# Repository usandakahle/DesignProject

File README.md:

# Micromouse Power Module System

This project is the power module circuit for the EEE3088F design project that provides power to the micromouse system

## Features

-  Boost Converter (3.7V → 5V @ 1.5A)
-  LDO Regulator (5V → 3.3V @ 300mA)
-  Dual H-Bridge Motor Driver (DRV8833 for 4x brushed DC motors)
-  High-Side Load Switches (TPS2HB50-Q1, 2 channels @ 1A each)
-  Physical ON/OFF switch with <30µA shutdown current
-  USB-C Female Connector
-  CH224K PD Negotiation (9V)
-  Linear Voltage Regulator, LM7805 (5V)
-  LiPo Battery Charging IC, TC4056A
-  Small PCB footprint, JLCPCB-ready
-  -All features and components are sourced from JLCPCB (https://jlcpcb.com/parts/all-electronic-components) 
  
---

##  Design Overview

- Input: 3.7V Li-ion (1S1P)
- USB-C Input: 9V
- Voltage Regulation:
  - Boost: MT3608
  - 3.3V Regulator: AMS1117-3.3 or TLV75533P
  - 5V Regulator: LM7805
- Motor Driver: DRV8833, controls 4 DC motors bidirectionally
- Load Switches:TPS2HB50-Q1 with configurable ILIM resistors
- ON/OFF Circuit: Slide switch + pMOS + NPN low-quiescent design

---

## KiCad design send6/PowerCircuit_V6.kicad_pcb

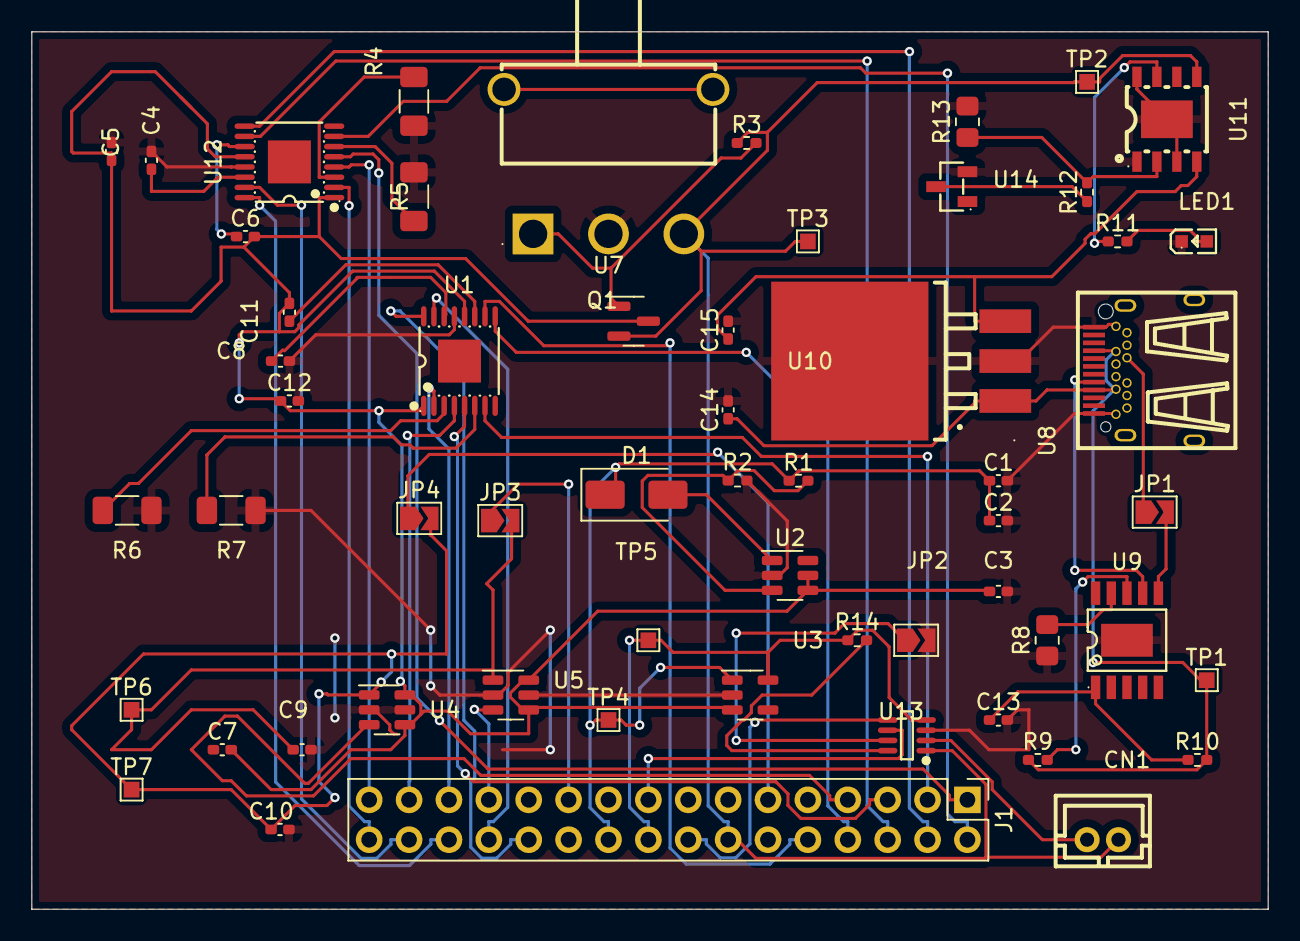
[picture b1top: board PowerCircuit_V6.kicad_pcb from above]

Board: 2 copper layers, 78.7 x 55.9 mm, 58 parts (0 on the bottom side), 55 nets.

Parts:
C1, C2, C3, C7, C9, C10, C13: 1uF; C_0402_1005Metric_Pad0.74x0.62mm_HandSolder
C4, C8: 2.2 uF; C_0402_1005Metric_Pad0.74x0.62mm_HandSolder
C5, C12: 10 uF; C_0402_1005Metric_Pad0.74x0.62mm_HandSolder
C6, C11: 10nF; C_0402_1005Metric_Pad0.74x0.62mm_HandSolder
C14, C15: 10uF; C_0402_1005Metric_Pad0.74x0.62mm_HandSolder
CN1: B2B-PH-K-S(LF)(SN); CONN-TH_B2B-PH-K-S
D1: D_Schottky; D_SMA
J1: Conn_02x16_Odd_Even; PinHeader_2x16_P2.54mm_Vertical
JP1, JP2, JP3, JP4: Jumper_2_Open; SolderJumper-2_P1.3mm_Open_TrianglePad1.0x1.5mm
LED1: KT-0603R; LED0603-RD
Q1: AO3401A; SOT-23
R1: 75k; R_0402_1005Metric_Pad0.72x0.64mm_HandSolder
R2, R9: 10k; R_0402_1005Metric_Pad0.72x0.64mm_HandSolder
R3: 47k; R_0402_1005Metric_Pad0.72x0.64mm_HandSolder
R4, R5, R6, R7: 1; R_1206_3216Metric_Pad1.30x1.75mm_HandSolder
R8: 6.8k; R_0805_2012Metric_Pad1.20x1.40mm_HandSolder
R10, R11, R14: 1k; R_0402_1005Metric_Pad0.72x0.64mm_HandSolder
R12: 2k; R_0402_1005Metric_Pad0.72x0.64mm_HandSolder
R13: 5.6k; R_0805_2012Metric_Pad1.20x1.40mm_HandSolder
TP1, TP2, TP3: TestPoint; TestPoint_Pad_1.0x1.0mm
TP4: 5V out; TestPoint_Pad_1.0x1.0mm
TP5: 3.3V out; TestPoint_Pad_1.0x1.0mm
TP6: External Load out; TestPoint_Pad_1.0x1.0mm
TP7: Ext load out; TestPoint_Pad_1.0x1.0mm
U1, U12: DRV8833PWP; TSSOP-16_L5.0-W4.4-P0.65-LS6.4-BL-EP
U2: MT3608; SOT-23-6
U3: AP2112K-3.3; SOT-23-5
U4, U5: TPS22929D; SOT-23-6
U7: K3-1391B-51; SW-TH_K3-1391B-51
U8: FUC-24F11-SNLB1; USB-C-SMD_C67380
U9: CH224K; ESSOP-10_L4.9-W3.9-P1.0-LS6.0-TL-EP
U10: LM7805S/TR; TO-263-3_L8.6-W10.2-P2.54-LS14.4-BR
U11: TC4056A; ESOP-8_L4.9-W3.9-P1.27-LS6.0-BR-EP3.3
U13: INA219AIDCNR; SOT-23-8_L3.0-W1.7-P0.65-LS2.8-BR
U14: MMBT2222A_C8512; SOT-23-3_L2.9-W1.3-P1.90-LS2.4-BR

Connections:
/3V3: J1.18, R14.1, TP5.1, U3.5 (VOUT), U13.4 (VS)
/5V: C1.1, C2.1, D1.1 (K), J1.20, R1.1, TP4.1, U3.1 (VIN)
/BATTERY: CN1.1, J1.14, Q1.2 (S), R3.1, TP2.1, TP3.1, U7.3, U11.5 (BAT), U13.1 (IN+)
/BATT_OUT: CN1.2, U13.2 (IN-)
/CC1: U8.A5 (CC1), U9.7 (CC1)
/CC2: JP1.2 (B), U9.6 (CC2)
/CTRL_EXT_LOAD1: J1.25, U5.3 (ON)
/CTRL_EXT_LOAD2: J1.7, U4.3 (ON)
/EXT_LOAD1_OUT: J1.21, JP3.1 (A)
/EXT_LOAD2_OUT: J1.11, JP4.1 (A)
/I2C1_SCL: J1.16, U13.5 (SCL)
/I2C1_SDA: J1.17, U13.6 (SDA)
/MOTOR1_A_OUT: J1.32, U12.2 (AOUT1)
/MOTOR1_B_OUT: J1.31, U12.4 (AOUT2)
/MOTOR1_CTRL1: J1.28, U12.16 (AIN1)
/MOTOR1_CTRL2: J1.30, U12.15 (AIN2)
/MOTOR2_A_OUT: J1.2, U12.7 (BOUT1)
/MOTOR2_B_OUT: J1.1, U12.5 (BOUT2)
/MOTOR2_CTRL1: J1.4, U12.9 (BIN1)
/MOTOR2_CTRL2: J1.6, U12.10 (BIN2)
/MOTOR3_A_OUT: J1.27, U1.2 (AOUT1)
/MOTOR3_B_OUT: J1.29, U1.4 (AOUT2)
/MOTOR3_CTRL1: J1.24, U1.16 (AIN1)
/MOTOR3_CTRL2: J1.26, U1.15 (AIN2)
/MOTOR4_A_OUT: J1.3, U1.7 (BOUT1)
/MOTOR4_B_OUT: J1.5, U1.5 (BOUT2)
/MOTOR4_CTRL1: J1.8, U1.9 (BIN1)
/MOTOR4_CTRL2: J1.10, U1.10 (BIN2)
/PROG: R12.2, R13.1, U11.2 (PROG)
/PWR_OUT: C3.1, C5.1, C6.2, C7.2, C11.2, C12.1, Q1.3 (D), U1.1 (nSleep), U1.12 (VM), U2.4 (EN), U2.5 (IN), U3.3 (EN), U4.4 (VIN), U4.6 (VIN), U5.4 (VIN), U5.6 (VIN), U12.1 (nSleep), U12.12 (VM)
/Step_5V: C15.1, U10.3 (OUT), U11.4 (VCC)
/VBUS: C14.1, R9.1, R10.2, TP1.1, U8.A4 (VBUS), U8.A9 (VBUS), U8.B4 (VBUS), U8.B9 (VBUS), U10.1 (VCC)
GND: C1.2, C2.2, C3.2, C4.2, C5.2, C7.1, C8.2, C9.2, C10.2, C12.2, C13.2, C14.2, C15.2, J1.19, J1.23, JP2.2 (B), LED1.1 (K), R2.2, R4.1, R5.2, R6.1, R7.2, R8.1, R13.2, U1.13 (GND), U2.2 (GND), U3.2 (GND), U4.2 (GND), U4.5 (GND), U5.2 (GND), U5.5 (GND), U7.2, U8.A1 (GND), U8.A12 (GND), U8.B1 (GND), U8.B12 (GND), U9.11 (GND), U10.2 (GND), U10.4 (GND), U11.1 (TEMP), U11.3 (GND), U11.8 (CE), U11.9 (EP), U12.13 (GND), U13.3 (GND), U14.2 (E)
unnamed: D1.2 (A), U2.1 (SW)
unnamed: JP1.1 (A), U8.B5 (CC2)
unnamed: JP2.1 (A), U13.7 (A0)
unnamed: C9.1, JP3.2 (B), TP6.1, U5.1 (VOUT)
unnamed: C10.1, JP4.2 (B), TP7.1, U4.1 (VOUT)
unnamed: LED1.2 (A), R11.2
unnamed: Q1.1 (G), R3.2, U7.1
unnamed: R6.2, U1.3 (AISEN)
unnamed: R7.1, U1.6 (BISEN)
unnamed: C11.1, U1.11 (VCP)
unnamed: C8.1, U1.14 (VINT)
unnamed: R1.2, R2.1, U2.3 (FB)
unnamed: R8.2, U9.9 (CFG1)
unnamed: R9.2, U9.8 (VBUS)
unnamed: C13.1, R10.1, U9.1 (VDD)
unnamed: R11.1, U11.7 (CHRG)
unnamed: R4.2, U12.3 (AISEN)
unnamed: R5.1, U12.6 (BISEN)
unnamed: C6.1, U12.11 (VCP)
unnamed: C4.1, U12.14 (VINT)
unnamed: R14.2, U13.8 (A1)
unnamed: R12.1, U14.3 (C)

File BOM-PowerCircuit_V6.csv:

Comment,Designator,Footprint,LCSC,Quantity
1k,"R10,R11,R14",R_0402_1005Metric_Pad0.72x0.64mm_HandSolder,C11702,3
2.2 uF,"C4,C8",C_0402_1005Metric_Pad0.74x0.62mm_HandSolder,C12530,2
AO3401A,Q1,SOT-23,C15127,1
10nF,C6,C_0402_1005Metric_Pad0.74x0.62mm_HandSolder,C15195,1
10nF,"C11,C12,C14,C15,C5",C_0402_1005Metric_Pad0.74x0.62mm_HandSolder,C15525,5
6.8k,R8,R_0805_2012Metric_Pad1.20x1.40mm_HandSolder,C17772,1
1,"R4,R5,R6,R7",R_1206_3216Metric_Pad1.30x1.75mm_HandSolder,C17928,4
KT-0603R,LED1,LED0603-RD,C2286,1
75k,R1,R_0603_1608Metric_Pad0.98x0.95mm_HandSolder,C23242,1
D_Schottky,D1,D_SMA,C2480,1
10k,"R2,R9",R_0402_1005Metric_Pad0.72x0.64mm_HandSolder,C25744,2
47k,R3,R_0402_1005Metric_Pad0.72x0.64mm_HandSolder,C25792,1
2k,R12,R_0402_1005Metric_Pad0.72x0.64mm_HandSolder,C4109,1
TPS22929D,"U4,U5",SOT-23-6,C415177,2
5.6k,R13,R_0805_2012Metric_Pad1.20x1.40mm_HandSolder,C4382,1
DRV8833PWP,"U1,U12",TSSOP-16_L5.0-W4.4-P0.65-LS6.4-BL-EP,C50506,2
LM7805S/TR,U10,TO-263-3_L8.6-W10.2-P2.54-LS14.4-BR,C507146,1
AP2112K-3.3,U3,SOT-23-5,C51118,1
1uF,"C1,C10,C13,C2,C3,C7,C9",C_0402_1005Metric_Pad0.74x0.62mm_HandSolder,C52923,7
FUC-24F11-SNLB1,U8,USB-C-SMD_C67380,C67380,1
TC4056A,U11,ESOP-8_L4.9-W3.9-P1.27-LS6.0-BR-EP3.3,C84051,1
MT3608,U2,SOT-23-6,C84817,1
MMBT2222A_C8512,U14,SOT-23-3_L2.9-W1.3-P1.90-LS2.4-BR,C8512,1
INA219AIDCNR,U13,SOT-23-8_L3.0-W1.7-P0.65-LS2.8-BR,C87469,1
K3-1391B-51,U7,SW-TH_K3-1391B-51,C92656,1
CH224K,U9,ESSOP-10_L4.9-W3.9-P1.0-LS6.0-TL-EP,C970725,1
External Load out,TP6,TestPoint_Pad_1.0x1.0mm,,1
TestPoint,TP3,TestPoint_Pad_1.0x1.0mm,,1
Jumper_2_Open,JP3,SolderJumper-2_P1.3mm_Open_TrianglePad1.0x1.5mm,,1
TestPoint,TP2,TestPoint_Pad_1.0x1.0mm,,1
3.3V out,TP5,TestPoint_Pad_1.0x1.0mm,,1
Jumper_2_Open,JP1,SolderJumper-2_P1.3mm_Open_TrianglePad1.0x1.5mm,,1
5V out,TP4,TestPoint_Pad_1.0x1.0mm,,1
Jumper_2_Open,JP4,SolderJumper-2_P1.3mm_Open_TrianglePad1.0x1.5mm,,1
Jumper_2_Open,JP2,SolderJumper-2_P1.3mm_Open_TrianglePad1.0x1.5mm,,1
Ext load out,TP7,TestPoint_Pad_1.0x1.0mm,,1
TestPoint,TP1,TestPoint_Pad_1.0x1.0mm,,1

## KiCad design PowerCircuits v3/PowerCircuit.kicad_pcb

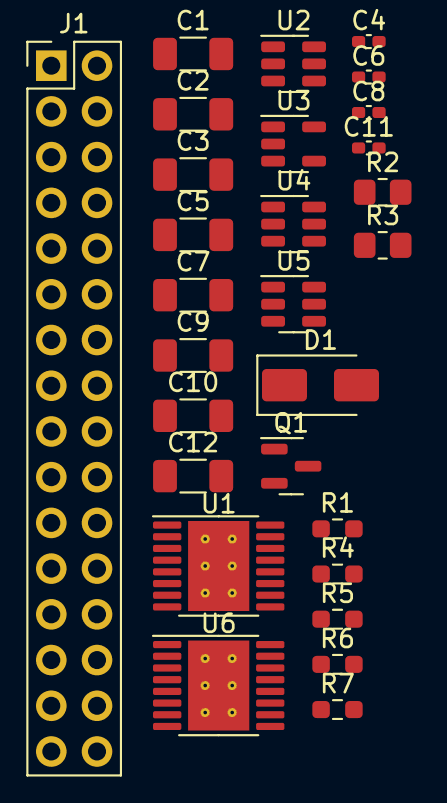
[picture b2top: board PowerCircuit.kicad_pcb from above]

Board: 2 copper layers, 28 parts (0 on the bottom side), 36 nets, no tracks yet.

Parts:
C1, C3, C7, C9, C10: 1uF; C_1206_3216Metric_Pad1.33x1.80mm_HandSolder
C2: 1 uF; C_1206_3216Metric_Pad1.33x1.80mm_HandSolder
C4, C11: 2.2 uF; C_0402_1005Metric_Pad0.74x0.62mm_HandSolder
C5, C12: 10 uF; C_1206_3216Metric_Pad1.33x1.80mm_HandSolder
C6, C8: 0.01uF; C_0402_1005Metric_Pad0.74x0.62mm_HandSolder
D1: D_Schottky; D_SMA
J1: Conn_02x16_Odd_Even; PinHeader_2x16_P2.54mm_Vertical
Q1: AO3401A; SOT-23
R1: 75k; R_0603_1608Metric_Pad0.98x0.95mm_HandSolder
R2: 10k; R_0805_2012Metric_Pad1.20x1.40mm_HandSolder
R3: 47k; R_0805_2012Metric_Pad1.20x1.40mm_HandSolder
R4, R5: 1; R_0603_1608Metric_Pad0.98x0.95mm_HandSolder
R6, R7: 0.4; R_0603_1608Metric_Pad0.98x0.95mm_HandSolder
U1, U6: DRV8833PWP; HTSSOP-16-1EP_4.4x5mm_P0.65mm_EP3.4x5mm_Mask2.46x2.31mm_The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
U2: MT3608; SOT-23-6
U3: AP2112K-3.3; SOT-23-5
U4, U5: TPS22929D; SOT-23-6

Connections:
/3V3: J1.18, U3.5 (VOUT)
/5V: C1.1, C2.1, D1.1 (K), J1.20, R1.1, U3.1 (VIN)
/BATTERY: J1.14, Q1.2 (S), R3.1
/CTRL_EXT_LOAD1: J1.25, U5.3 (ON)
/CTRL_EXT_LOAD2: J1.7, U4.3 (ON)
/EXT_LOAD1_OUT: C9.1, J1.21, U5.1 (VOUT)
/EXT_LOAD2_OUT: C10.1, J1.11, U4.1 (VOUT)
/MOTOR1_A_OUT: J1.32, U1.2 (AOUT1)
/MOTOR1_B_OUT: J1.31, U1.4 (AOUT2)
/MOTOR1_CTRL1: J1.28, U1.16 (AIN1)
/MOTOR1_CTRL2: J1.30, U1.15 (AIN2)
/MOTOR2_A_OUT: J1.2, U1.7 (BOUT1)
/MOTOR2_B_OUT: J1.1, U1.5 (BOUT2)
/MOTOR2_CTRL1: J1.4, U1.9 (BIN1)
/MOTOR2_CTRL2: J1.6, U1.10 (BIN2)
/MOTOR3_A_OUT: J1.27, U6.2 (AOUT1)
/MOTOR3_B_OUT: J1.29, U6.4 (AOUT2)
/MOTOR3_CTRL1: J1.24, U6.16 (AIN1)
/MOTOR3_CTRL2: J1.26, U6.15 (AIN2)
/MOTOR4_A_OUT: J1.3, U6.7 (BOUT1)
/MOTOR4_B_OUT: J1.5, U6.5 (BOUT2)
/MOTOR4_CTRL1: J1.8, U6.9 (BIN1)
/MOTOR4_CTRL2: J1.10, U6.10 (BIN2)
/PWR_OUT: C3.1, C5.1, C6.2, C7.2, C8.2, C12.1, Q1.3 (D), U1.1 (nSLEEP), U1.12 (VM), U2.4 (EN), U2.5 (IN), U3.3 (EN), U4.4 (VIN), U4.6 (VIN), U5.4 (VIN), U5.6 (VIN), U6.1 (nSLEEP), U6.12 (VM)
GND: C1.2, C2.2, C3.2, C4.2, C5.2, C7.1, C9.2, C10.2, C11.2, C12.2, J1.19, J1.23, R2.2, R4.1, R5.2, R6.2, R7.1, U1.13 (GND), U1.17 (GND(PPAD)), U2.2 (GND), U3.2 (GND), U4.2 (GND), U4.5 (GND), U5.2 (GND), U5.5 (GND), U6.13 (GND), U6.17 (GND(PPAD))
unnamed: D1.2 (A), U2.1 (SW)
unnamed: Q1.1 (G), R3.2
unnamed: R4.2, U1.3 (AISEN)
unnamed: R5.1, U1.6 (BISEN)
unnamed: C6.1, U1.11 (VCP)
unnamed: C4.1, U1.14 (VINT)
unnamed: R1.2, R2.1, U2.3 (FB)
unnamed: R6.1, U6.3 (AISEN)
unnamed: R7.2, U6.6 (BISEN)
unnamed: C8.1, U6.11 (VCP)
unnamed: C11.1, U6.14 (VINT)

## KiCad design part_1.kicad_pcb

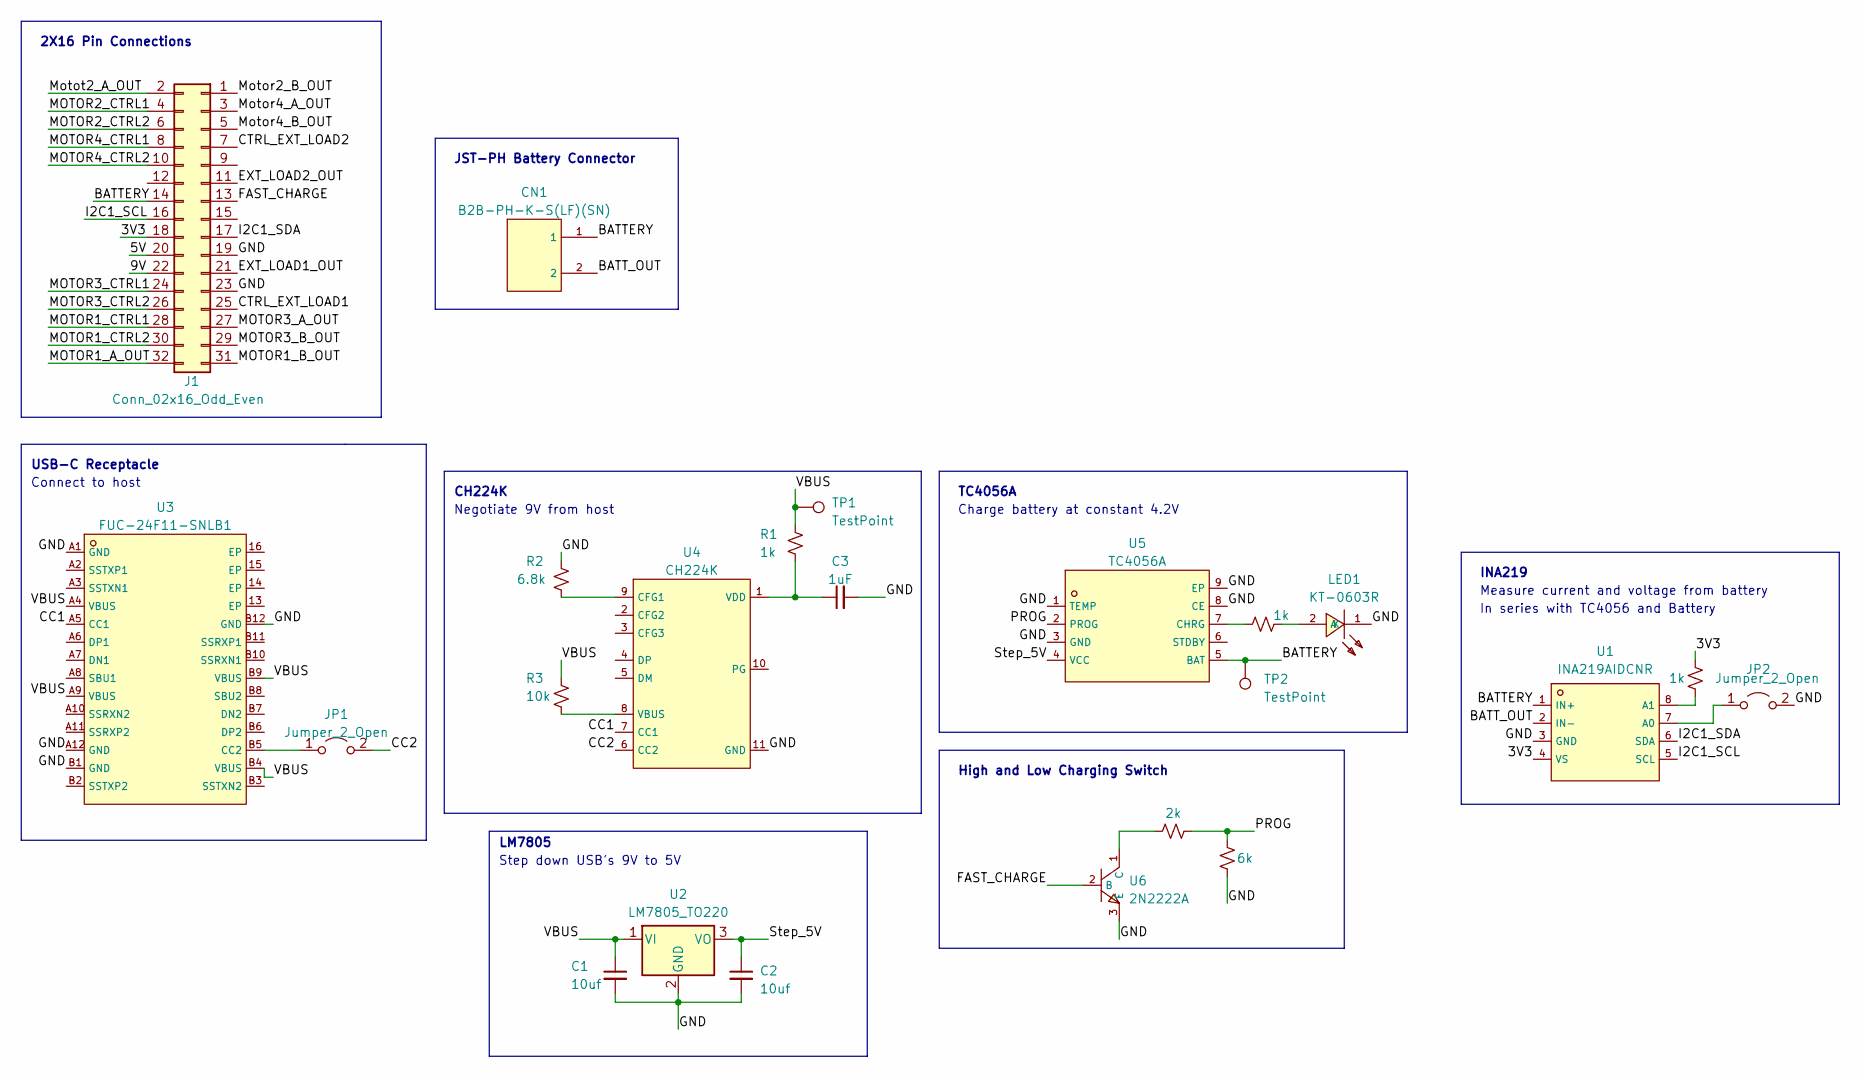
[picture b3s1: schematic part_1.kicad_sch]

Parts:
C1, C2: 10uf; C_0402_1005Metric_Pad0.74x0.62mm_HandSolder
C3: 1uF; C_0402_1005Metric_Pad0.74x0.62mm_HandSolder
CN1: B2B-PH-K-S(LF)(SN); CONN-TH_B2B-PH-K-S; LCSC C131337
J1: Conn_02x16_Odd_Even; PinHeader_2x16_P2.54mm_Vertical
JP1, JP2: Jumper_2_Open; SolderJumper-2_P1.3mm_Open_TrianglePad1.0x1.5mm
LED1: KT-0603R; LED0603-RD; LCSC C2286
R1, R4, R5: 1k; R_0402_1005Metric_Pad0.72x0.64mm_HandSolder
R2: 6.8k; R_0402_1005Metric_Pad0.72x0.64mm_HandSolder
R3: 10k; R_0402_1005Metric_Pad0.72x0.64mm_HandSolder
R6: 2k; R_0402_1005Metric_Pad0.72x0.64mm_HandSolder
R10: 6k; R_0402_1005Metric_Pad0.72x0.64mm_HandSolder
TP1, TP2: TestPoint; TestPoint_Pad_1.0x1.0mm
U1: INA219AIDCNR; SOT-23-8_L3.0-W1.7-P0.65-LS2.8-BR; LCSC C87469
U2: LM7805_TO220; TO-220-3_Vertical
U3: FUC-24F11-SNLB1; USB-C-SMD_C67380; Part # C67380
U4: CH224K; ESSOP-10_L4.9-W3.9-P1.0-LS6.0-TL-EP; Part # C970725
U5: TC4056A; ESSOP-10_L4.9-W3.9-P1.0-LS6.0-TL-EP; LCSC C84051
U6: 2N2222A; TO-92-3_L4.8-W3.7-P2.54-R; LCSC C358533

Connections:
/3V3: J1.18, R5.1, U1.4 (VS)
/5V: J1.20
/9V: J1.22
/BATTERY: CN1.1, J1.14, TP2.1, U1.1 (IN+), U5.5 (BAT)
/BATT_OUT: CN1.2, U1.2 (IN-)
/CC1: U3.A5 (CC1), U4.7 (CC1)
/CC2: JP1.2 (B), U4.6 (CC2)
/CTRL_EXT_LOAD1: J1.25
/CTRL_EXT_LOAD2: J1.7
/EXT_LOAD1_OUT: J1.21
/EXT_LOAD2_OUT: J1.11
/FAST_CHARGE: J1.13, U6.2 (B)
/GND: C1.2, C2.2, C3.2, J1.19, J1.23, JP2.2 (B), LED1.1 (K), R2.1, R10.2, U1.3 (GND), U2.2 (GND), U3.A1 (GND), U3.A12 (GND), U3.B1 (GND), U3.B12 (GND), U4.11 (GND), U5.1 (TEMP), U5.3 (GND), U5.8 (CE), U5.9 (EP), U6.3 (E)
/I2C1_SCL: J1.16, U1.5 (SCL)
/I2C1_SDA: J1.17, U1.6 (SDA)
/MOTOR1_A_OUT: J1.32
/MOTOR1_B_OUT: J1.31
/MOTOR1_CTRL1: J1.28
/MOTOR1_CTRL2: J1.30
/MOTOR2_CTRL1: J1.4
/MOTOR2_CTRL2: J1.6
/MOTOR3_A_OUT: J1.27
/MOTOR3_B_OUT: J1.29
/MOTOR3_CTRL1: J1.24
/MOTOR3_CTRL2: J1.26
/MOTOR4_CTRL1: J1.8
/MOTOR4_CTRL2: J1.10
/Motor2_B_OUT: J1.1
/Motor4_A_OUT: J1.3
/Motor4_B_OUT: J1.5
/Motot2_A_OUT: J1.2
/PROG: R6.2, R10.1, U5.2 (PROG)
/Step_5V: C2.1, U2.3 (VO), U5.4 (VCC)
/VBUS: C1.1, R1.2, R3.1, TP1.1, U2.1 (VI), U3.A4 (VBUS), U3.A9 (VBUS), U3.B4 (VBUS), U3.B9 (VBUS)
unnamed: JP1.1 (A), U3.B5 (CC2)
unnamed: JP2.1 (A), U1.7 (A0)
unnamed: LED1.2 (A), R4.2
unnamed: R5.2, U1.8 (A1)
unnamed: R2.2, U4.9 (CFG1)
unnamed: R3.2, U4.8 (VBUS)
unnamed: C3.1, R1.1, U4.1 (VDD)
unnamed: R4.1, U5.7 (CHRG)
unnamed: R6.1, U6.1 (C)

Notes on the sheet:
High and Low Charging Switch
2X16 Pin Connections
Measure current and voltage from battery
Charge battery at constant 4.2V
TC4056A
Step down USB's 9V to 5V
LM7805
Connect to host
In series with TC4056 and Battery
INA219
Negotiate 9V from host
CH224K
JST-PH Battery Connector
USB-C Receptacle

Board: 2 copper layers, 23 parts (0 on the bottom side), 21 nets, no tracks yet.

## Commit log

2025-03-26 git repo made for the project
2025-03-26 Adding files despite line-ending warnings
2025-03-27 Final Sanda parts schematic
2025-03-27 Create JLC Components
2025-03-27 Version 3
2025-03-27 New Components Added
2025-03-28 Final Zipped Submission
2025-04-23 Final Design (3D,pcb)
2025-04-25 README.md
2025-05-16 BOM and CPL Files from JLCPCB Tools
